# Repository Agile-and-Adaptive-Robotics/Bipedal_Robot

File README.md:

# Bipedal Robot
The bipedal robot is a cross disciplinary project being worked on in the Agile and Adaptive Robotics lab by PhD, Masters, and Undergraduate Students. The aim is to develop a robot, actuated by pneumatic artificial muscles, that is able to walk.

## Current Objectives
1. Create a Matlab script to optimize PAM placement to replicate human torque profile about joints.
2. Design lower body skeletal structure that has the range of motion of a human skeletal structure.

## Future Objective
1. Print and assemble lower body of the bipedal robot.
2. Perform experiments to verify the torque profiles about joints.
3. Develop a sequence of actuation that can generate sagittal plane walking motion.
4. Create a neural controller that can integrate sensory information to generate robust walking.

## Software
SolidWorks - Tools for creating the model of the lower body, to be printed on Markforge 3D printers.

OpenSim - Used to display biologically realistic muscle placements on human.

Matlab - For creating scripts for torque calculation and muscle placement optimization.

Animatlab - Neural network simulations for a bipedal walker.

## Contributors
Ben Bolen - Project Co-Lead, PhD Student

Connor Morrow - Project Co-Lead, PhD Student

Harold Omotoy - Muscle Placement and PAM Testing, Undergraduate Researcher

## Previous Contributors
Alex Steele - Knee Joint Designer, Past Master's Student

Ty Fitzgerald - Ankle and Foot Design, Undergraduate Researcher 

David Pleshakov - Lower Body Design, Undergraduate Researcher

Mick Leungpathomaram - Various SolidWorks components and assemblies, High School Research Intern

Alaina Clar - Various SolidWorks components and naming convention creator, High School Research Intern

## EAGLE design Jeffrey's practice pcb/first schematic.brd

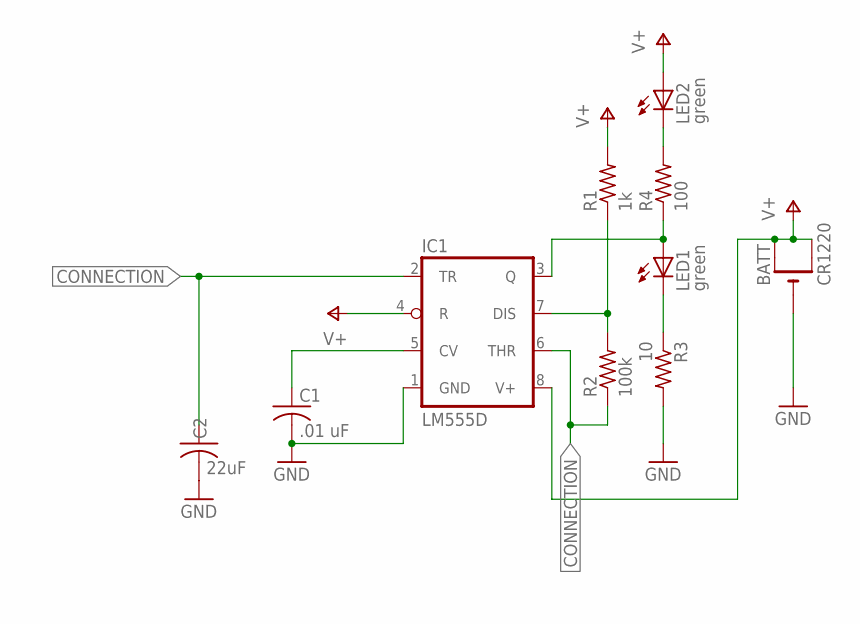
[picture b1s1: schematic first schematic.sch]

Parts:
BATT: CR1220; CR1220-SMD
C1: .01 uF; C0805; MPN CDR31BX103AKZS
C2: 22uF; C0805
IC1: LM555D; SO08
LED1, LED2: green; CHIPLED_0805
R1: 1k; R0805
R2: 100k; R0805
R3: 10; R0805
R4: 100; R0805

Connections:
CONNECTION: C2.1, IC1.2 (TR), IC1.6 (THR), R2.1
GND: BATT.-, C1.2, C2.2, IC1.1 (GND), R3.2
unnamed: IC1.3 (Q), LED1.A, R4.1
unnamed: LED2.C, R4.2
unnamed: LED1.C, R3.1
unnamed: IC1.7 (DIS), R1.1, R2.2
unnamed: C1.1, IC1.5 (CV)
V+: BATT.+$1 (+), BATT.+$2 (+1), IC1.4 (R), IC1.8 (V+), LED2.A, R1.2

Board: 2 copper layers, 10 parts (0 on the bottom side), 8 nets, no tracks yet.

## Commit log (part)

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2026-06-26 Fixed tendon error
2026-06-28 Fixing optimizer
    Is my k_b matrix incorrect? Need to investigate.
2026-06-29 methodology fix
    MonoPam..._balance now matches methodology of minimizeFlx. However, the calculation of equivalent stiffness k_eff now needs to be changed for all the optimizers.
2026-06-29 Updated optimization results
    need to pick the correct one from minimizeExt10mmX3 minimizeExtX3. Check filtered results.
